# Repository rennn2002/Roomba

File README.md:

# Roomba
3D printed desktop cleaner robot.

[Model is available here](https://a360.co/34pWwOY)

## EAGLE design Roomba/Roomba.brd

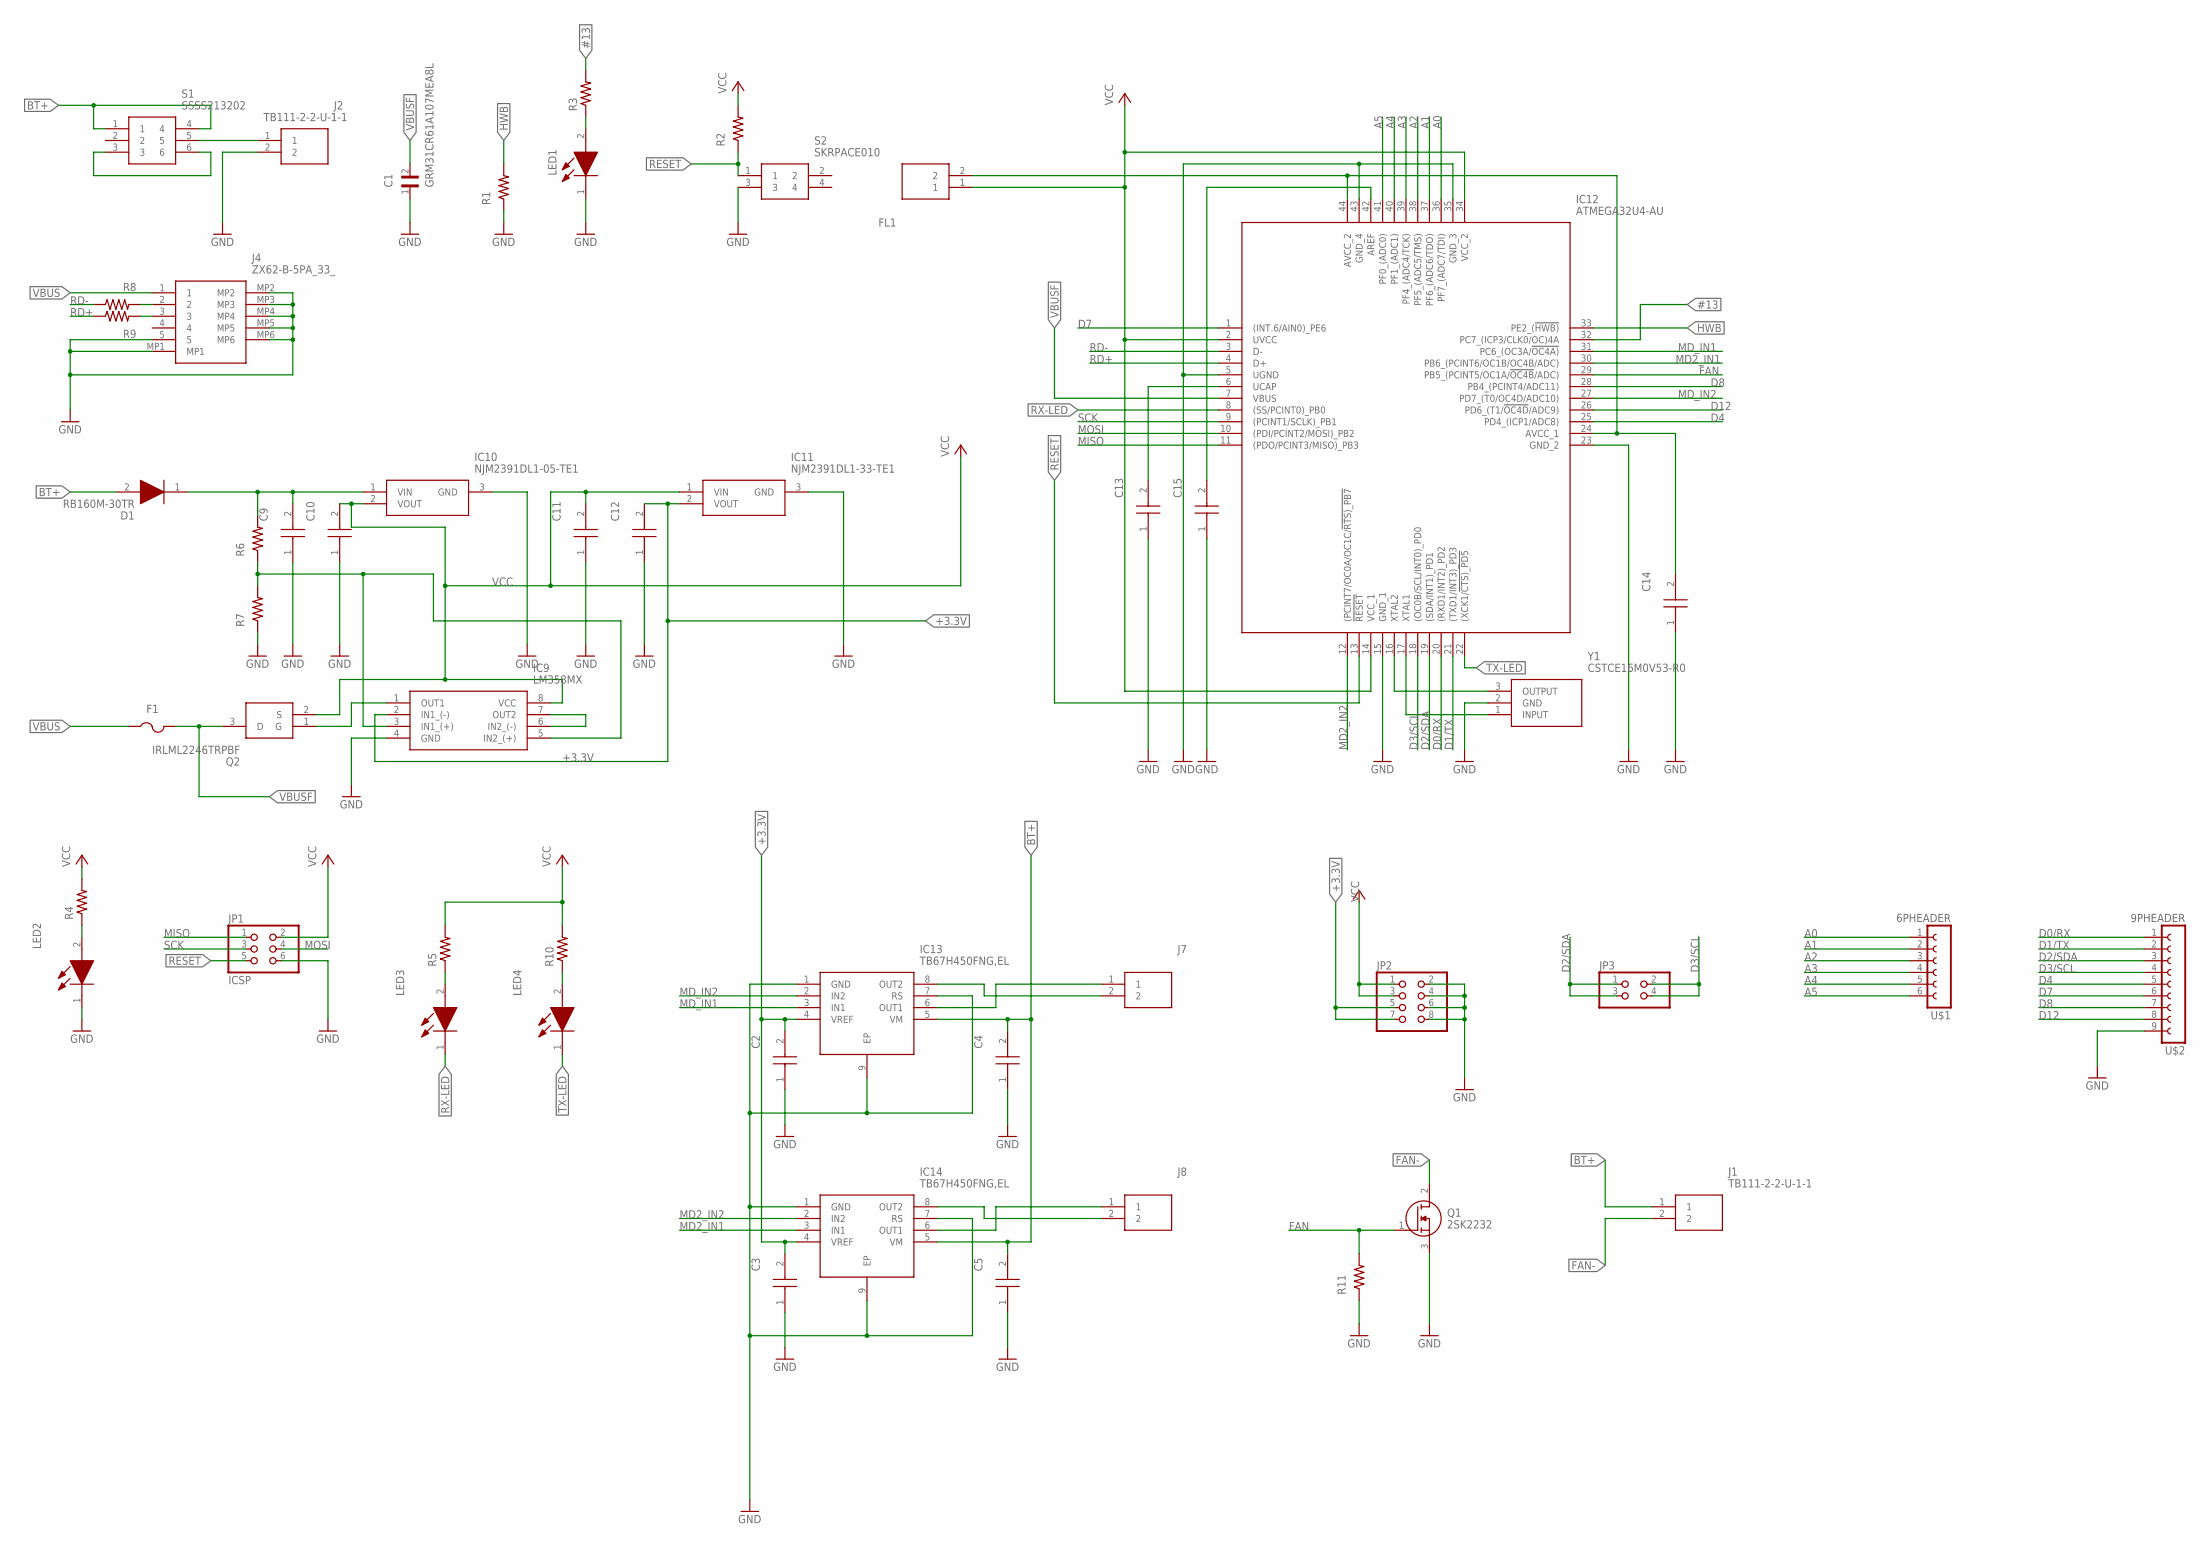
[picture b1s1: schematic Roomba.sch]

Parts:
C1: GRM31CR61A107MEA8L; CAPC3216X190N
C2, C3, C4, C5, C9, C11, C15: GRM188F11H104ZA01B; CAPC1608X90N
C10, C12: GRM31CB31A476KE15L; CAPC3216X180N
C13, C14: GRM188R71E105KA12D; CAPC1608X90N
D1: RB160M-30TR; SODFL3516X90N
F1: MF-MSMF010-2; FUSC4632X110N
FL1: BLM18PG600SN1D; BLM18AG102BH1D
IC9: LM358MX; SOIC127P600X175-8N
IC10: NJM2391DL1-05-TE1; TO-252-3-L1_1
IC11: NJM2391DL1-33-TE1; TO-252-3-L1
IC12: ATMEGA32U4-AU; QFP80P1200X1200X120-44N
IC13, IC14: TB67H450FNG,EL; SOIC127P600X175-9N
J1, J2, J7, J8: TB111-2-2-U-1-1; TB11122U11
J4: ZX62-B-5PA_33_; ZX62B5PA33
JP1: ICSP; 2X03
JP2: POWER; 2X04
JP3: I2C; 2X02
LED1, LED3, LED4: SML-E12Y8WT86; SMLE12Y8WT86
LED2: SML-E12P8WT86; LEDC1608X36N
Q1: 2SK2232; TO254P470X1000X2090-3P
Q2: IRLML2246TRPBF; SOT95P237X112-3N
R1, R2, R6, R7, R11: CRCW120610K0FKEA; RESC3216X60N
R3, R4, R5, R10: CRCW12061K00FKEA; RESC3216X60N
R8, R9: CRCW120622R0FKEA; RESC3216X60N
S1: SSSS213202
S2: SKRPACE010; SMT(4.2X3.2)
U$1: 6PHEADER; HDRVR6W70P254_1X6_1574X250X850B
U$2: 9PHEADER; HDRVR9W70P254_1X9_2336X250X850B
Y1: CSTCE16M0V53-R0; CSTCE16M0V53R0

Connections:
#13: IC12.32 (PC7_(ICP3/CLK0/OC)4A), R3.2
+3.3V: C2.2, C3.2, C12.2, IC9.2 (IN1_(-)), IC11.2 (VOUT), IC13.4 (VREF), IC14.4 (VREF), JP2.5, JP2.7
A0: IC12.36 (PF7_(ADC7/TDI)), U$1.1
A1: IC12.37 (PF6_(ADC6/TDO)), U$1.2
A2: IC12.38 (PF5_(ADC5/TMS)), U$1.3
A3: IC12.39 (PF4_(ADC4/TCK)), U$1.4
A4: IC12.40 (PF1_(ADC1)), U$1.5
A5: IC12.41 (PF0_(ADC0)), U$1.6
BT+: C4.2, C5.2, D1.2 (A), IC13.5 (VM), IC14.5 (VM), J1.1, S1.1, S1.4
D0/RX: IC12.20 ((RXD1/INT2)_PD2), U$2.1
D1/TX: IC12.21 ((TXD1/INT3)_PD3), U$2.2
D2/SDA: IC12.19 ((SDA/INT1)_PD1), JP3.1, JP3.3, U$2.3
D3/SCL: IC12.18 ((OC0B/SCL/INT0)_PD0), JP3.2, JP3.4, U$2.4
D4: IC12.25 (PD4_(ICP1/ADC8)), U$2.5
D7: IC12.1 ((INT.6/AIN0)_PE6), U$2.6
D8: IC12.28 (PB4_(PCINT4/ADC11)), U$2.7
D12: IC12.26 (PD6_(T1/!OC4D!/ADC9)), U$2.8
FAN: IC12.29 (PB5_(PCINT5/OC1A/!OC4B!/ADC)), Q1.1 (G), R11.2
FAN-: J1.2, Q1.2 (D)
GND: C1.1, C2.1, C3.1, C4.1, C5.1, C9.1, C10.1, C11.1, C12.1, C13.1, C14.1, C15.1, IC9.4 (GND), IC10.3 (GND), IC11.3 (GND), IC12.5 (UGND), IC12.15 (GND_1), IC12.23 (GND_2), IC12.35 (GND_3), IC12.43 (GND_4), IC13.1 (GND), IC13.7 (RS), IC13.9 (EP), IC14.1 (GND), IC14.7 (RS), IC14.9 (EP), J2.2, J4.5, J4.MP1, J4.MP2, J4.MP3, J4.MP4, J4.MP5, J4.MP6, JP1.6, JP2.2, JP2.4, JP2.6, JP2.8, LED1.1 (K), LED2.1 (K), Q1.3 (S), R1.1, R7.1, R11.1, S2.3, U$2.9, Y1.2 (GND)
HWB: IC12.33 (PE2_(!HWB)), R1.2
MD2_IN1: IC12.30 (PB6_(PCINT6/OC1B/OC4B/ADC)), IC14.3 (IN1)
MD2_IN2: IC12.12 ((PCINT7/OC0A/OC1C/!RTS)_PB7), IC14.2 (IN2)
MD_IN1: IC12.31 (PC6_(OC3A/!OC4A)), IC13.3 (IN1)
MD_IN2: IC12.27 (PD7_(T0/OC4D/ADC10)), IC13.2 (IN2)
MISO: IC12.11 ((PDO/PCINT3/MISO)_PB3), JP1.1
MOSI: IC12.10 ((PDI/PCINT2/MOSI)_PB2), JP1.4
unnamed: LED1.2 (A), R3.1
unnamed: LED2.2 (A), R4.1
unnamed: LED3.2 (A), R5.1
unnamed: LED4.2 (A), R10.1
unnamed: IC9.6 (IN2_(-)), IC9.7 (OUT2)
unnamed: J2.1, S1.5
unnamed: S1.3, S1.6
unnamed: IC9.3 (IN1_(+)), IC9.5 (IN2_(+)), R6.1, R7.2
unnamed: C9.2, D1.1 (K), IC10.1 (VIN), R6.2
unnamed: IC9.1 (OUT1), Q2.1 (G)
unnamed: J4.2, R8.2
unnamed: J4.3, R9.2
unnamed: C13.2, IC12.6 (UCAP)
unnamed: C14.2, FL1.2, IC12.24 (AVCC_1), IC12.44 (AVCC_2)
unnamed: IC12.17 (XTAL1), Y1.1 (INPUT)
unnamed: IC12.16 (XTAL2), Y1.3 (OUTPUT)
unnamed: C15.2, IC12.42 (AREF)
unnamed: IC13.6 (OUT1), J7.1
unnamed: IC13.8 (OUT2), J7.2
unnamed: IC14.8 (OUT2), J8.2
unnamed: IC14.6 (OUT1), J8.1
RD+: IC12.4 (D+), R9.1
RD-: IC12.3 (D-), R8.1
RESET: IC12.13 (!RESET), JP1.5, R2.1, S2.1
RX-LED: IC12.8 ((SS/PCINT0)_PB0), LED3.1 (K)
SCK: IC12.9 ((PCINT1/SCLK)_PB1), JP1.3
TX-LED: IC12.22 ((XCK1/!CTS)_PD5), LED4.1 (K)
VBUS: F1.1, J4.1
VBUSF: C1.2, F1.2, IC12.7 (VBUS), Q2.3 (D)
VCC: C10.2, C11.2, FL1.1, IC9.8 (VCC), IC10.2 (VOUT), IC11.1 (VIN), IC12.2 (UVCC), IC12.14 (VCC_1), IC12.34 (VCC_2), JP1.2, JP2.1, JP2.3, Q2.2 (S), R2.2, R4.2, R5.2, R10.2

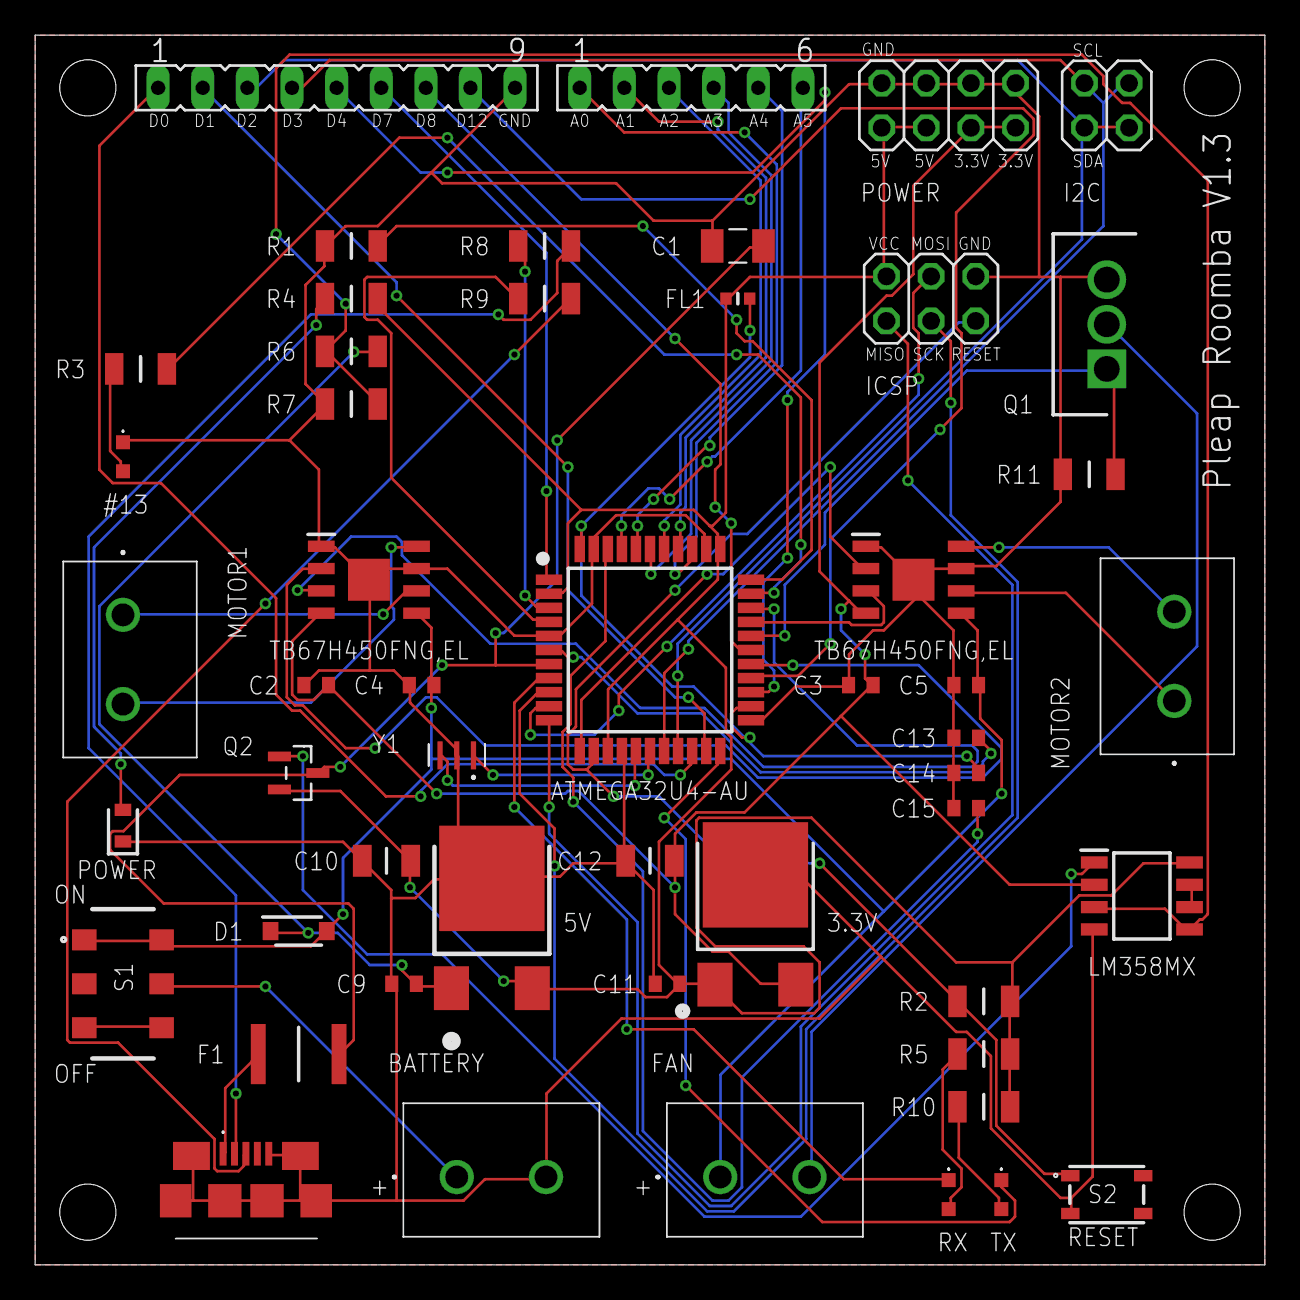
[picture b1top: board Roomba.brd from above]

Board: 2 copper layers, 70.0 x 70.0 mm, 51 parts (0 on the bottom side), 57 nets.

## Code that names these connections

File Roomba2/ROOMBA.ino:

const int MD_IN1 = 5;
const int MD_IN2 = 6;
const int MD2_IN1 = 10;
const int MD2_IN2 = 11;

const int FAN = 13;

const int IR_R = 3;
const int IR_L = 2; //not used

int isObstacle = HIGH;

void MD_forward(int rate) {
  analogWrite(MD_IN1, rate);
  analogWrite(MD_IN2, 0);
}

void MD2_forward(int rate) {
  analogWrite(MD2_IN1, rate);
  analogWrite(MD2_IN2, 0);
}
void MD_backward(int rate) {
  analogWrite(MD_IN1, 0);
  analogWrite(MD_IN2, rate);
}

void MD2_backward(int rate) {
  analogWrite(MD2_IN1, 0);
  analogWrite(MD2_IN2, rate);
}

void MD_brake() {
  digitalWrite(MD_IN1, HIGH);
  digitalWrite(MD_IN2, HIGH);
}

void MD2_brake() {
  digitalWrite(MD2_IN1, HIGH);
  digitalWrite(MD2_IN2, HIGH);
}

void setup() {
  pinMode(MD_IN1,OUTPUT);
  pinMode(MD_IN2,OUTPUT);
  pinMode(MD2_IN1,OUTPUT);
  pinMode(MD2_IN2,OUTPUT);
  
  pinMode(FAN,OUTPUT);
  pinMode(IR_R, INPUT);
  pinMode(IR_L, INPUT);

  Serial.begin(9600);
}

void loop() {
  digitalWrite(FAN,HIGH);
  
  isObstacle = digitalRead(IR_L);

  if (isObstacle == LOW){
    //safe
    Serial.println("safe");
    MD_forward(100);
    MD2_forward(100);
  } else {
    //fall
    Serial.println("fall");
    MD_backward(100);
    MD2_backward(100);
    delay(2000);
    MD_forward(100);
    MD2_backward(100);
    delay(1500);
  }
delay(20);
}

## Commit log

2021-03-09 latest
2022-01-29 Jan 29, 2022
